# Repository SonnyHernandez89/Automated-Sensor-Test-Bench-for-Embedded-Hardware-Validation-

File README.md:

# Automated Sensor Test Bench for Embedded Hardware Validation

This project is an ESP32-based hardware validation platform designed to test embedded sensor modules, verify communication, detect failures, and generate pass/fail results.

## Current Progress
- Designed a custom KiCad PCB for sensor testing
- Added fabrication files for PCB manufacturing
- Built initial ESP-IDF C++ project structure
- Completed first UART ping-pong communication test
- Preparing I2C sensor validation tests

## Tools Used
ESP32, ESP-IDF, C++, KiCad, UART, I2C, Git/GitHub

## Goal
The goal of this project is to create a repeatable test bench for validating sensors through wiring, firmware testing, continuity checks, and documented pass/fail results.

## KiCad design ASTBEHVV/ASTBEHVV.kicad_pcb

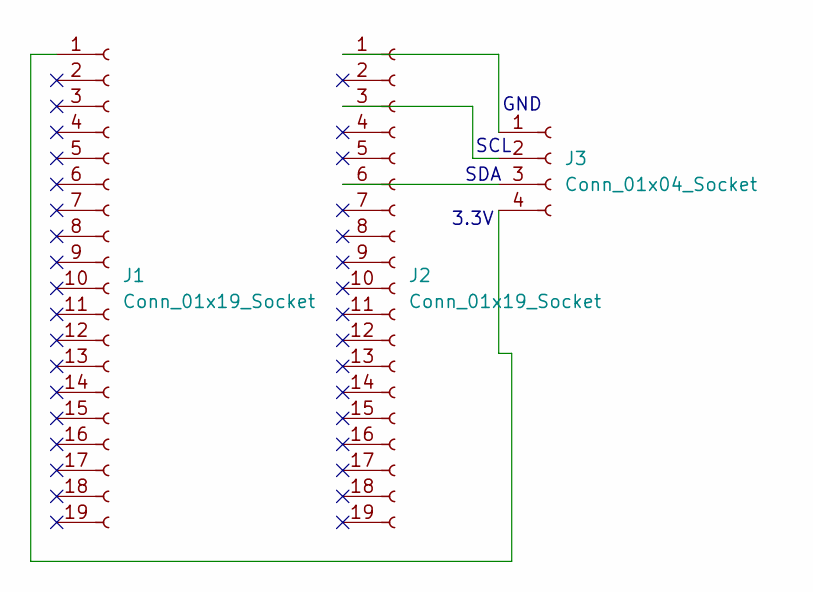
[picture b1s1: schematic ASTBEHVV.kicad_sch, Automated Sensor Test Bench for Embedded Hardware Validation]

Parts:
J1, J2: Conn_01x19_Socket; PinHeader_1x19_P2.54mm_Vertical
J3: Conn_01x04_Socket; PinHeader_1x04_P2.54mm_Vertical

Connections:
unnamed: J1.1, J3.4
unnamed: J2.1, J3.1
unnamed: J2.3, J3.2
unnamed: J2.6, J3.3

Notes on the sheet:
GND
3.3V
SDA
SCL

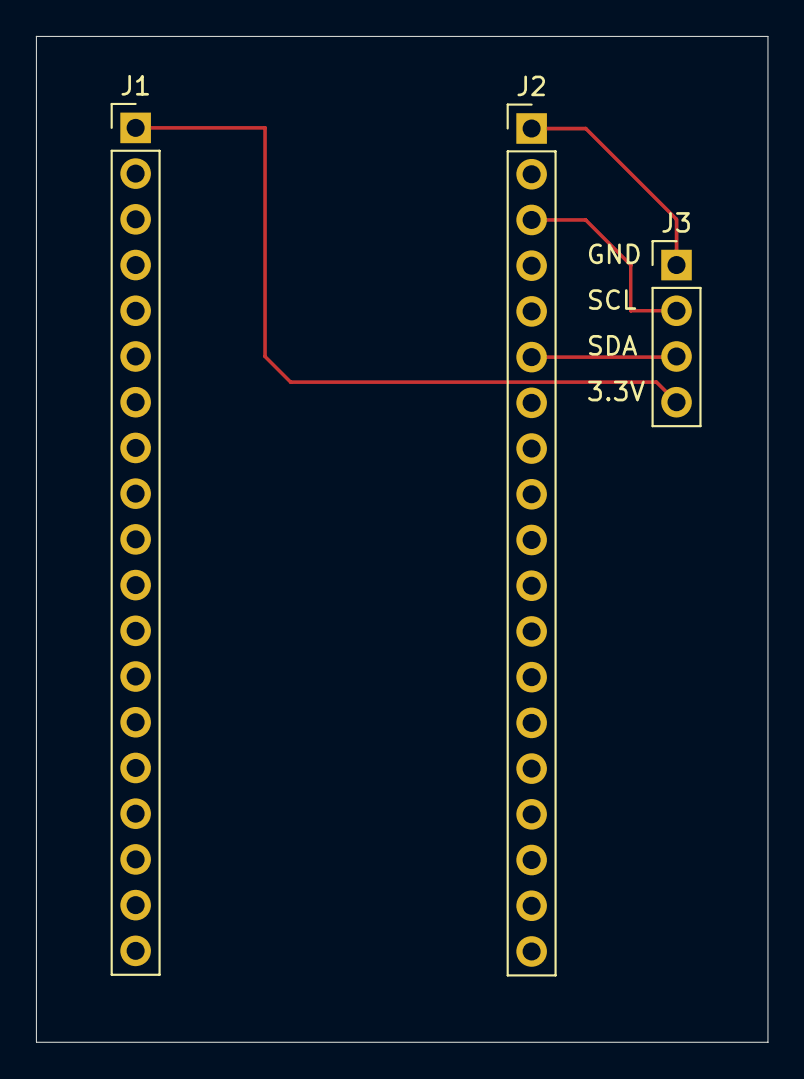
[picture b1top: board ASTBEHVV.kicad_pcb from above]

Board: 2 copper layers, 40.6 x 55.9 mm, 3 parts (0 on the bottom side), 4 nets.

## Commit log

2026-06-11 added KiCADfiles and ping-pong test001
2026-06-11 Update README with project and file descriptions
    Added project details and descriptions for files related to the automated sensor test bench.
2026-06-13 Added Test Case Directory
2026-06-13 added edge case protection
2026-06-24 added T002 functionality for 8 bit sensor i.e BME280 sensor
2026-06-24 Fixed sensor register not displaying for 2-byte registers like the INE219
2026-06-30 Revise README for clarity and project details
    Updated project description and added sections for current progress, tools used, and project goals.
